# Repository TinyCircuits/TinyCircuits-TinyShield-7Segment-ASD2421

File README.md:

# TinyCircuits TinyShield 7 Segment Display
# ASD2421 Rev2

The design files are located under design_files/ for the TinyCircuits ASD2421 Rev 2 PCB.  This is a Tiny shield board (Square Version, 20mm x 20mm) that has two seven segment displays (Red LEDs).  

Format is in Cadsoft Eagle format - Eagle version 6.2 was used for the original design.

For more infomation on this, check out the product page at TinyCircuits.com:  https://tinycircuits.com/collections/leds-displays/products/7-segment-display-tinyshield

# License:

Design by TinyCircuits.
All design files are released under the Creative Commons Attribution Share-Alike 3.0 License, see the following link for details: http://creativecommons.org/licenses/by-sa/3.0

All text above must be included in any redistribution or derived design

This project uses designs and concepts developed as part of the Arduino project and the LilyPad project.  The TinyCircuits design files themselves (schematics, PCB and libraries) are not directly derived from these works' design files and have been created new, however the concepts and basic architecture behind the TinyDuino and TinyLily products are derived and we thank the hard work of the organizations below for their contributions to open-source hardware:
  
Original Arduino Uno Design by Team Arduino

LilyPad Arduino Design by Leah Buechley and Sparkfun Electronics

Please support the open-source hardware community

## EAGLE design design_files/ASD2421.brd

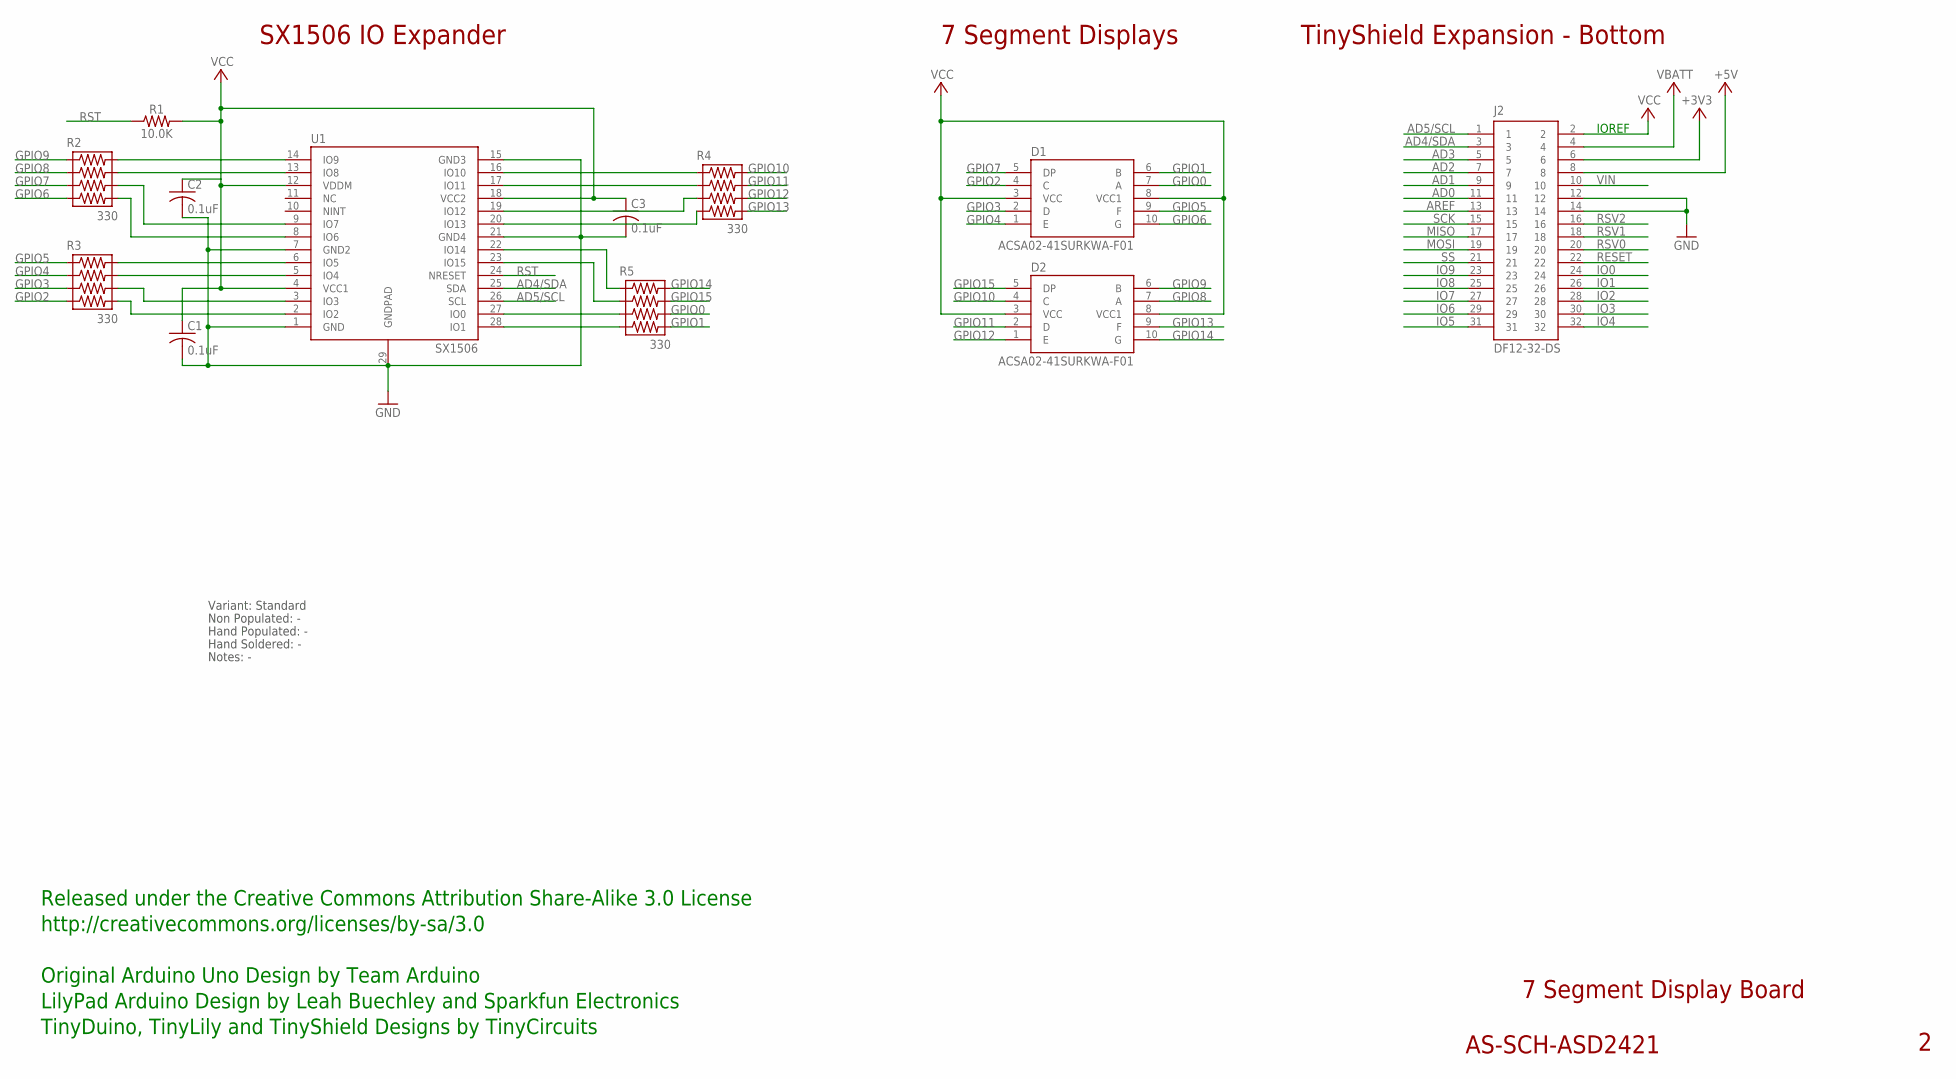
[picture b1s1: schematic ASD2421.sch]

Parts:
C1, C2, C3: 0.1uF; C0402
D1, D2: ACSA02-41SURKWA-F01; PARTNO AS-ITM-00133
J2: DF12-32-DS; PARTNO AS-ITM-00012
R1: 10.0K; 0402
R2, R3, R4, R5: 330; 0402RPACK
U1: SX1506; PARTNO AS-ITM-00134

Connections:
+3V3: J2.6
+5V: J2.8
AD0: J2.11
AD1: J2.9
AD2: J2.7
AD3: J2.5
AD4/SDA: J2.3, U1.25 (SDA)
AD5/SCL: J2.1, U1.26 (SCL)
AREF: J2.13
GND: C1.2, C2.2, C3.2, J2.12, J2.14, U1.1 (GND), U1.7 (GND2), U1.15 (GND3), U1.21 (GND4), U1.29 (GNDPAD)
GPIO0: D1.7 (A), R5.6
GPIO1: D1.6 (B), R5.8
GPIO2: D1.4 (C), R3.7
GPIO3: D1.2 (D), R3.5
GPIO4: D1.1 (E), R3.3
GPIO5: D1.9 (F), R3.1
GPIO6: D1.10 (G), R2.7
GPIO7: D1.5 (DP), R2.5
GPIO8: D2.7 (A), R2.3
GPIO9: D2.6 (B), R2.1
GPIO10: D2.4 (C), R4.2
GPIO11: D2.2 (D), R4.4
GPIO12: D2.1 (E), R4.6
GPIO13: D2.9 (F), R4.8
GPIO14: D2.10 (G), R5.2
GPIO15: D2.5 (DP), R5.4
IO0: J2.24
IO1: J2.26
IO2: J2.28
IO3: J2.30
IO4: J2.32
IO5: J2.31
IO6: J2.29
IO7: J2.27
IO8: J2.25
IO9: J2.23
MISO: J2.17
MOSI: J2.19
unnamed: R2.2, U1.14 (IO9)
unnamed: R2.4, U1.13 (IO8)
unnamed: R2.6, U1.9 (IO7)
unnamed: R2.8, U1.8 (IO6)
unnamed: R3.2, U1.6 (IO5)
unnamed: R3.4, U1.5 (IO4)
unnamed: R3.6, U1.3 (IO3)
unnamed: R3.8, U1.2 (IO2)
unnamed: R4.1, U1.16 (IO10)
unnamed: R4.3, U1.17 (IO11)
unnamed: R4.5, U1.19 (IO12)
unnamed: R4.7, U1.20 (IO13)
unnamed: R5.1, U1.22 (IO14)
unnamed: R5.3, U1.23 (IO15)
unnamed: R5.5, U1.27 (IO0)
unnamed: R5.7, U1.28 (IO1)
RESET: J2.22
RST: R1.1, U1.24 (NRESET)
RSV0: J2.20
RSV1: J2.18
RSV2: J2.16
SCK: J2.15
SS: J2.21
VBATT: J2.4
VCC: C1.1, C2.1, C3.1, D1.3 (VCC), D1.8 (VCC1), D2.3 (VCC), D2.8 (VCC1), J2.2, R1.2, U1.4 (VCC1), U1.12 (VDDM), U1.18 (VCC2)
VIN: J2.10

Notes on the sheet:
TinyShield Expansion - Bottom
7 Segment Display Board
AS-SCH-ASD2421
IOREF
Released under the Creative Commons Attribution Share-Alike 3.0 License
http://creativecommons.org/licenses/by-sa/3.0
LilyPad Arduino Design by Leah Buechley and Sparkfun Electronics
TinyDuino, TinyLily and TinyShield Designs by TinyCircuits
Original Arduino Uno Design by Team Arduino
SX1506 IO Expander
7 Segment Displays
Non Populated: -
Hand Populated: -
Hand Soldered: -
Notes: -
Variant: Standard

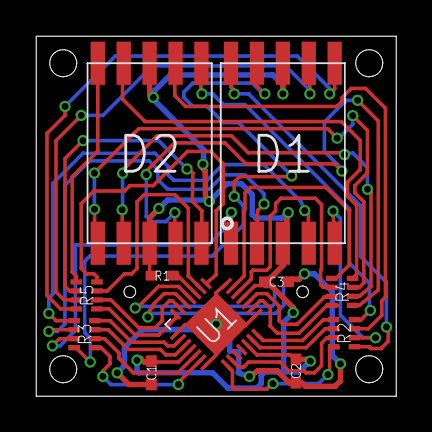
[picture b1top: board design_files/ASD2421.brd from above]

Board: 2 copper layers, 20.0 x 20.0 mm, 13 parts (1 on the bottom side), 37 nets.

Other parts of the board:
U$1: DOCFIELD-TINYCIRCUITS-PCB

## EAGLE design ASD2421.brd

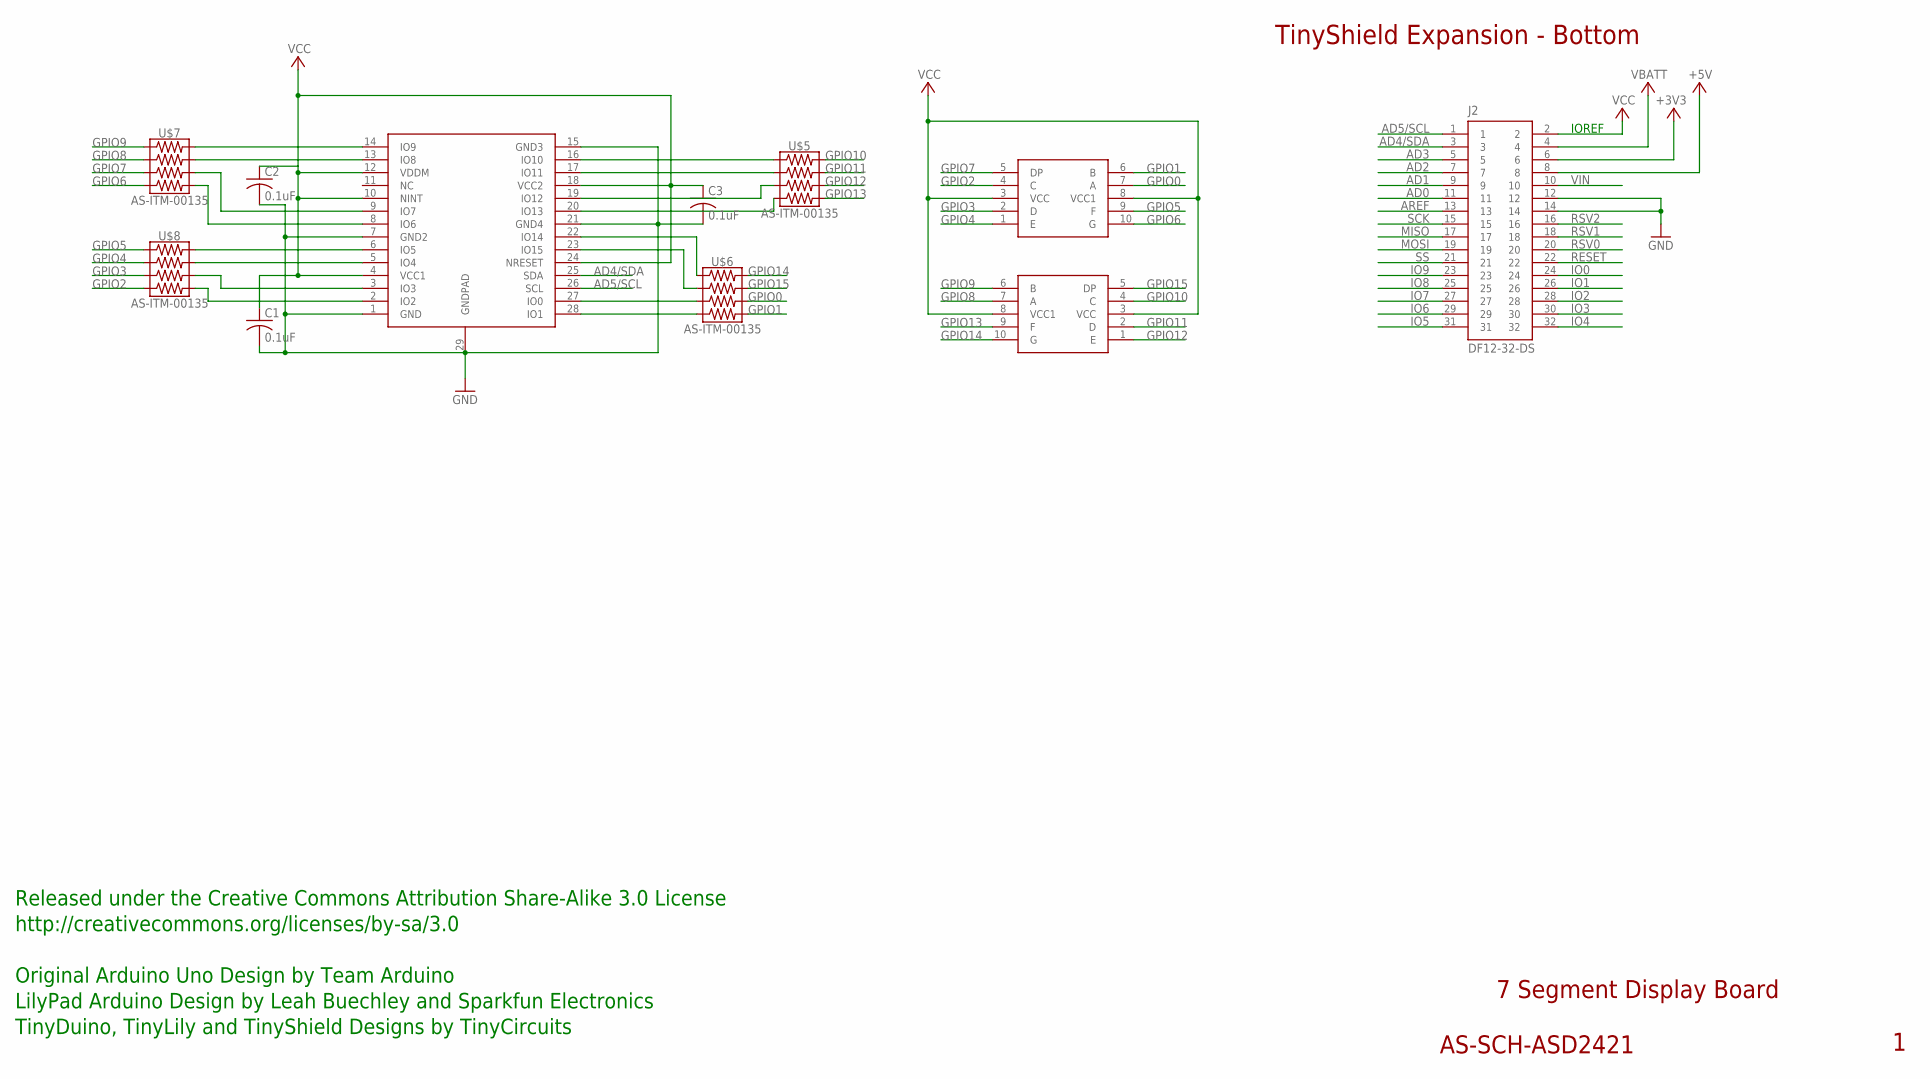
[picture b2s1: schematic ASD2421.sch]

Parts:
C1, C2, C3: 0.1uF; C0402
J2: DF12-32-DS; PARTNO AS-ITM-00012
U$2, U$3: AS-ITM-00133; ACSA02-41SURKWA-F01
U$4: AS-ITM-00134; SX1506
U$5, U$6, U$7, U$8: AS-ITM-00135; 0402RPACK

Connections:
+3V3: J2.6
+5V: J2.8
AD0: J2.11
AD1: J2.9
AD2: J2.7
AD3: J2.5
AD4/SDA: J2.3, U$4.25 (SDA)
AD5/SCL: J2.1, U$4.26 (SCL)
AREF: J2.13
GND: C1.2, C2.2, C3.2, J2.12, J2.14, U$4.1 (GND), U$4.7 (GND2), U$4.15 (GND3), U$4.21 (GND4), U$4.29 (GNDPAD)
GPIO0: U$2.7 (A), U$6.6
GPIO1: U$2.6 (B), U$6.8
GPIO2: U$2.4 (C), U$8.7
GPIO3: U$2.2 (D), U$8.5
GPIO4: U$2.1 (E), U$8.3
GPIO5: U$2.9 (F), U$8.1
GPIO6: U$2.10 (G), U$7.7
GPIO7: U$2.5 (DP), U$7.5
GPIO8: U$3.7 (A), U$7.3
GPIO9: U$3.6 (B), U$7.1
GPIO10: U$3.4 (C), U$5.2
GPIO11: U$3.2 (D), U$5.4
GPIO12: U$3.1 (E), U$5.6
GPIO13: U$3.9 (F), U$5.8
GPIO14: U$3.10 (G), U$6.2
GPIO15: U$3.5 (DP), U$6.4
IO0: J2.24
IO1: J2.26
IO2: J2.28
IO3: J2.30
IO4: J2.32
IO5: J2.31
IO6: J2.29
IO7: J2.27
IO8: J2.25
IO9: J2.23
MISO: J2.17
MOSI: J2.19
unnamed: U$4.14 (IO9), U$7.2
unnamed: U$4.13 (IO8), U$7.4
unnamed: U$4.9 (IO7), U$7.6
unnamed: U$4.8 (IO6), U$7.8
unnamed: U$4.6 (IO5), U$8.2
unnamed: U$4.5 (IO4), U$8.4
unnamed: U$4.3 (IO3), U$8.6
unnamed: U$4.2 (IO2), U$8.8
unnamed: U$4.16 (IO10), U$5.1
unnamed: U$4.17 (IO11), U$5.3
unnamed: U$4.19 (IO12), U$5.5
unnamed: U$4.20 (IO13), U$5.7
unnamed: U$4.22 (IO14), U$6.1
unnamed: U$4.23 (IO15), U$6.3
unnamed: U$4.27 (IO0), U$6.5
unnamed: U$4.28 (IO1), U$6.7
RESET: J2.22
RSV0: J2.20
RSV1: J2.18
RSV2: J2.16
SCK: J2.15
SS: J2.21
VBATT: J2.4
VCC: C1.1, C2.1, C3.1, J2.2, U$2.3 (VCC), U$2.8 (VCC1), U$3.3 (VCC), U$3.8 (VCC1), U$4.4 (VCC1), U$4.10 (NINT), U$4.12 (VDDM), U$4.18 (VCC2), U$4.24 (NRESET)
VIN: J2.10

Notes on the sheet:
TinyShield Expansion - Bottom
7 Segment Display Board
AS-SCH-ASD2421
IOREF
Released under the Creative Commons Attribution Share-Alike 3.0 License
http://creativecommons.org/licenses/by-sa/3.0
LilyPad Arduino Design by Leah Buechley and Sparkfun Electronics
TinyDuino, TinyLily and TinyShield Designs by TinyCircuits
Original Arduino Uno Design by Team Arduino

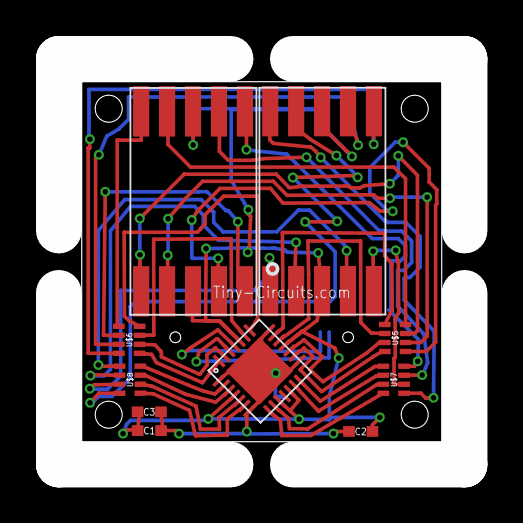
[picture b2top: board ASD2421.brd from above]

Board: 2 copper layers, 20.0 x 20.0 mm, 12 parts (1 on the bottom side), 36 nets.

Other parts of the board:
U$1: DOCFIELD-TINYCIRCUITS-PCB

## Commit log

2014-08-24 Updated Link
2019-01-02 Update Rev and Format
2019-01-07 updated comments
2019-05-15 added images
2019-05-15 added .zip file
2019-05-17 updated images
2019-05-20 corrected comments
2019-05-20 updated naming
2020-02-11 image update
2020-07-28 Add CAD data
2020-08-14 Update CAD drawing
